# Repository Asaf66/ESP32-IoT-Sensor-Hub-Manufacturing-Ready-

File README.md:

# ESP32-C3 Multi-Sensor IoT & Data Logger
hardware system based on ESP32-C3 (RISC-V architecture) on a 4-layer PCB for noise immunity. 

The project includes sensors (environment, light, and sound), smart power and charging management (MCP73871), and a user interface.
The system supports local data storage via SD card and external flash memory via SPI connection, with Wi-Fi and BLE connectivity.

1) All-in-One Sensing Solution: Integrated temperature, humidity, light, and sound sensors, eliminating the need for multiple external modules.
2) Industrial-Grade Reliability: The 4-layer design ensures the device operates without interference in noisy industrial environments.
3) Seamless Power Integration: Built-in USB-C charging and battery management, meaning your product is portable and user-friendly from day one.
4) Rapid Manufacturing: Delivered with a full production package (Gerbers, BOM, Pick-and-Place), optimized to minimize assembly errors and part costs.

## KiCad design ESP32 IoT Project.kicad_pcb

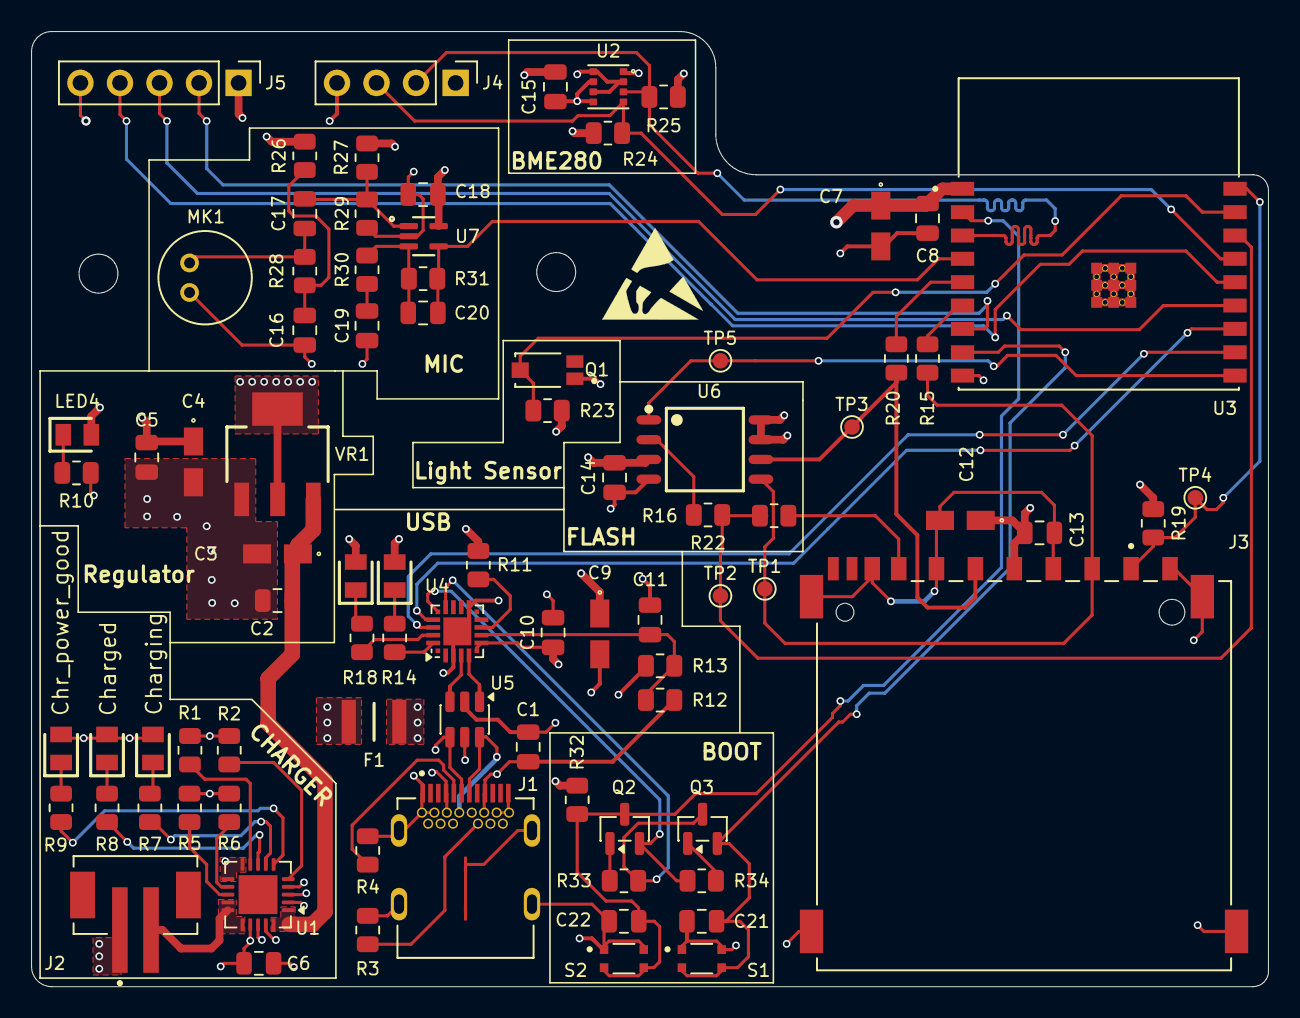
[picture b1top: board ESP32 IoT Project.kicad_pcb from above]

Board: 4 copper layers, 79.5 x 61.4 mm, 85 parts (0 on the bottom side), 58 nets.

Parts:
C1, C2, C5, C8, C10, C13, C14, C15, C18, C21: 0.1u; C_0805_2012Metric
C3, C4, C7, C12: 10u; T491A
C6, C11, C19, C22: 1u; C_0805_2012Metric
C9: 4.7u; T491A
C16: 0.1U; C_0805_2012Metric
C17: 0.01U; C_0805_2012Metric
C20: 100p; C_0805_2012Metric
F1: 0ZCH0110AF2E; FUSC3226X100N
J1: SS-52400-002; BELFUSE_SS-52400-002
J2: B2B-PH-SM4-TB; JST_B2B-PH-SM4-TB
J3: GSD090012SEU; AMPHENOL_GSD090012SEU
J4: Conn_01x04_Pin; PinHeader_1x04_P2.54mm_Vertical
J5: Conn_01x05_Pin; PinHeader_1x05_P2.54mm_Vertical
LED1, LED4, LED6: LTST-C170KRKT; LEDC2012X120N
LED2, LED5: LTST-C170GKT; LEDC2012X120N
LED3: LTST-C170TBKT; LEDC2012X120N
MK1: CMC-5042PF-AC; CUI_CMC-5042PF-AC
Q1: TEMT6000X01; TRANS_TEMT6000X01
Q2, Q3: BC817; SOT-23
R1, R2, R19, R23, R30, R32, R33, R34: 10K; R_0805_2012Metric
R3, R4: 5K1; R_0805_2012Metric
R5, R26, R28: 2K; R_0805_2012Metric
R6: 20K; R_0805_2012Metric
R7, R8, R9, R10, R14, R18: 470; R_0805_2012Metric
R11: 1K; R_0805_2012Metric
R12: 22K1; R_0805_2012Metric
R13: 47K5; R_0805_2012Metric
R15, R16, R20, R22: 50; R_0805_2012Metric
R24, R25: 4K7; R_0805_2012Metric
R27, R29: 1M; R_0805_2012Metric
R31: 100K; R_0805_2012Metric
S1: BOOT; SW_USLPT2819DT2TR
S2: RESET; SW_USLPT2819DT2TR
TP1, TP2, TP3, TP4, TP5: TestPoint; TestPoint_Pad_D1.0mm
U1: MCP73871-2CAI_ML; QFN-20-1EP_4x4mm_P0.5mm_EP2.5x2.5mm
U2: BME280; PSON65P250X250X100-8N
U3: ESP32-C3-WROOM-02-H4; MODULE_ESP32-C3-WROOM-02-H4
U4: CP2102N-Axx-xQFN20; SiliconLabs_QFN-20-1EP_3x3mm_P0.5mm_EP1.8x1.8mm
U5: USBLC6-2SC6; SOT-23-6
U6: W25Q32JVSSIQ; SOIC127P790X216-8N
U7: MAX4466EXK; SOT65P210X110-5N
VR1: LM1117MPX-3.3; VREG_LM1117MPX-3.3

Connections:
+3.3V: C4.1, C5.1, C7.1, C8.2, C9.1, C10.2, C12.1, C13.2, C14.2, C15.2, C18.1, J3.4 (VDD1), J4.1, J5.1, LED4.2 (A), LED5.2 (A), LED6.2 (A), R11.2, R19.1, R23.2, R24.2, R25.2, R26.2, R27.2, R32.1, U2.2 (CSB), U2.6 (VDDIO), U2.8 (VDD), U3.1 (3V3), U4.6 (VDD), U4.7 (VREGIN), U6.3 (~WP(IO2)), U6.7 (~HOLD/~RESET(IO3)), U6.8 (VCC), U7.5 (VCC), VR1.2 (VOUT_2), VR1.4 (VOUT_4)
+5V: C2.1, C3.1, U1.1 (OUT), U1.20 (OUT), VR1.3 (VIN)
/+5V_USB: C6.1, F1.2, LED1.2 (A), LED2.2 (A), LED3.2 (A), U1.2 (VPCC), U1.4 (PROG2), U1.17 (CE), U1.18 (IN), U1.19 (IN)
/Charged: R8.2, U1.8 (STAT1/~LBO)
/Charging: R9.2, U1.6 (~PG)
/Charging_power_good: R7.2, U1.7 (STAT2)
/ESP32-C3-02/BOOT: C21.1, Q3.2 (E), S1.3, S1.4, U3.8 (IO9)
/ESP32-C3-02/CS: TP5.1, U3.10 (IO10), U6.1 (~CS)
/ESP32-C3-02/CS_SD: J3.1 (CD/DAT3), R19.2, TP4.1, U3.18 (IO0)
/ESP32-C3-02/DTR: Q3.3 (C), R33.2, U4.15 (~CTS)
/ESP32-C3-02/EN: C22.1, Q2.3 (C), R32.2, S2.3, S2.4, U3.2 (EN)
/ESP32-C3-02/GPIO8: J5.2, U3.7 (IO8)
/ESP32-C3-02/GPIO18: J5.3, U3.13 (IO18)
/ESP32-C3-02/GPIO19: J5.4, U3.14 (IO19)
/ESP32-C3-02/MIC_OUT: C20.1, R31.1, U3.4 (IO5), U7.4 (OUT)
/ESP32-C3-02/MISO_DO: R16.1, R22.2, TP2.1, U3.16 (IO2)
/ESP32-C3-02/MOSI_DI: J3.2 (CMD), R15.1, TP1.1, U6.5 (DI(IO0))
/ESP32-C3-02/PHOTO_C: Q1.3, R23.1, U3.17 (IO1)
/ESP32-C3-02/RTS: Q2.2 (E), R34.2, U4.16 (~RTS)
/ESP32-C3-02/RX: U3.12 (TXD), U4.17 (RXD)
/ESP32-C3-02/SCL: J4.3, R24.1, U2.4 (SCK), U3.15 (IO3)
/ESP32-C3-02/SCLK: J3.5 (CLK), R20.2, TP3.1, U6.6 (CLK)
/ESP32-C3-02/SDA: J4.2, R25.1, U2.3 (SDI), U3.3 (IO4)
/ESP32-C3-02/TX: U3.11 (RXD), U4.18 (TXD)
/ESP32-C3-02/USB_D+: U4.4 (D+), U5.3 (I/O2)
/ESP32-C3-02/USB_D-: U4.5 (D-), U5.1 (I/O1)
/PWD__LED: LED4.1 (K), R10.1
/USB_DN: J1.A7 (DN1), J1.B7 (DN2), U5.6 (I/O1)
/USB_DP: J1.A6 (DP1), J1.B6 (DP2), U5.4 (I/O2)
/VBAT: J2.2, U1.14 (VBAT), U1.15 (VBAT), U1.16 (VBAT_SENSE)
/VBUS: C1.1, F1.1, J1.A4 (VBUSA1), J1.A9 (VBUSA2), J1.B4 (VBUSB1), J1.B9 (VBUSB2), R12.2, U5.5 (VBUS)
GND: C1.2, C2.2, C3.2, C4.2, C5.2, C6.2, C7.2, C8.1, C9.2, C10.1, C11.2, C12.2, C13.1, C14.1, C15.1, C16.2, C18.2, C19.2, C21.2, C22.2, J1.A1 (GNDA1), J1.A12 (GNDA2), J1.B1 (GNDB1), J1.B12 (GNDB2), J1.G1 (GND/SHIELD), J1.G2 (GND/SHIELD), J1.G3 (GND/SHIELD), J1.G4 (GND/SHIELD), J1.S1 (GND/SHIELD), J1.S2 (GND/SHIELD), J1.S3 (GND/SHIELD), J1.S4 (GND/SHIELD), J2.1, J3.3 (VSS1), J3.6 (VSS2), J3.8 (DAT1), J3.9 (DAT2), J3.G1 (SHIELD_GND), J3.G2 (SHIELD_GND), J3.G3 (SHIELD_GND), J3.G4 (SHIELD_GND), J4.4, J5.5, MK1.GND, Q1.1, R1.2, R2.2, R3.1, R4.1, R5.1, R6.1, R10.2, R13.1, R29.1, S1.1, S1.2, S2.1, S2.2, U1.3 (SEL), U1.10 (VSS), U1.11 (VSS), U2.1 (GND), U2.5 (SDO), U2.7 (GND), U3.9 (GND), U3.19 (GND), U3.20 (GND), U3.21 (GND), U3.22 (GND), U3.23 (GND), U3.24 (GND), U3.25 (GND), U3.26 (GND), U3.27 (GND), U3.28 (GND), U3.29 (GND), U3.30 (GND), U3.31 (GND), U3.32 (GND), U3.33 (GND), U3.34 (GND), U3.35 (GND), U3.36 (GND), U3.37 (GND), U3.38 (GND), U3.39 (GND), U4.3 (GND), U4.12 (GND), U4.21 (GND), U5.2 (GND), U6.4 (GND), U7.2 (GND), VR1.1 (GND)
unnamed: C16.1, R26.1, R28.2
unnamed: C17.1, MK1.OUT, R28.1
unnamed: C19.1, R30.1
unnamed: J1.A5 (CC1), R4.2
unnamed: J1.B5 (CC2), R3.2
unnamed: J3.7 (DAT0), R16.2
unnamed: LED1.1 (K), R9.1
unnamed: LED2.1 (K), R8.1
unnamed: LED3.1 (K), R7.1
unnamed: LED5.1 (K), R14.1
unnamed: LED6.1 (K), R18.1
unnamed: Q2.1 (B), R33.1
unnamed: Q3.1 (B), R34.1
unnamed: R5.2, U1.13 (PROG1)
unnamed: R6.2, U1.12 (PROG3)
unnamed: R2.1, U1.5 (THERM)
unnamed: R1.1, U1.9 (~TE)
unnamed: R20.1, U3.5 (IO6)
unnamed: R15.2, U3.6 (IO7)
unnamed: C11.1, R12.1, R13.2, U4.8 (VBUS)
unnamed: R11.1, U4.9 (~RST)
unnamed: R18.2, U4.19 (~RXT/GPIO.3)
unnamed: R14.2, U4.20 (~TXT/GPIO.2)
unnamed: R22.1, U6.2 (DO(IO1))
unnamed: C17.2, R27.1, R29.2, U7.1 (IN+)
unnamed: C20.2, R30.2, R31.2, U7.3 (IN-)

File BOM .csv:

Id,Designator,Footprint,Quantity,Designation,Supplier and ref
1,"R3,R4",R_0805_2012Metric,2,5K1,
2,"LED2,LED5",LEDC2012X120N,2,LTST-C170GKT,
3,R6,R_0805_2012Metric,1,20K,
4,"C2,C8,C18,C14,C5,C21,C1,C10,C15,C13",C_0805_2012Metric,10,0.1u,
5,R12,R_0805_2012Metric,1,22K1,
6,C16,C_0805_2012Metric,1,0.1U,
7,"LED4,LED6,LED1",LEDC2012X120N,3,LTST-C170KRKT,
8,"R5,R26,R28",R_0805_2012Metric,3,2K,
9,"C22,C11,C19,C6",C_0805_2012Metric,4,1u,
10,LED3,LEDC2012X120N,1,LTST-C170TBKT,
11,Q1,TRANS_TEMT6000X01,1,TEMT6000X01,
12,S2,SW_USLPT2819DT2TR,1,RESET,
13,U6,SOIC127P790X216-8N,1,W25Q32JVSSIQ,
14,"R7,R14,R9,R8,R18,R10",R_0805_2012Metric,6,470,
15,"R15,R22,R16,R20",R_0805_2012Metric,4,50,
16,U7,SOT65P210X110-5N,1,MAX4466EXK,
17,"R27,R29",R_0805_2012Metric,2,1M,
18,"R24,R25",R_0805_2012Metric,2,4K7,
19,U5,SOT-23-6,1,USBLC6-2SC6,
20,"TP3,TP5,TP4,TP2,TP1",TestPoint_Pad_D1.0mm,5,TestPoint,
21,J4,PinHeader_1x04_P2.54mm_Vertical,1,Conn_01x04_Pin,
22,U2,PSON65P250X250X100-8N,1,BME280,
23,"R23,R19,R33,R32,R34,R30,R2,R1",R_0805_2012Metric,8,10K,
24,J5,PinHeader_1x05_P2.54mm_Vertical,1,Conn_01x05_Pin,
25,"Q2,Q3",SOT-23,2,BC817,
26,U4,SiliconLabs_QFN-20-1EP_3x3mm_P0.5mm_EP1.8x1.8mm,1,CP2102N-Axx-xQFN20,
27,F1,FUSC3226X100N,1,0ZCH0110AF2E,
28,S1,SW_USLPT2819DT2TR,1,BOOT,
29,R11,R_0805_2012Metric,1,1K,
30,U3,MODULE_ESP32-C3-WROOM-02-H4,1,ESP32-C3-WROOM-02-H4,
31,U1,QFN-20-1EP_4x4mm_P0.5mm_EP2.5x2.5mm,1,MCP73871-2CAI_ML,
32,C9,T491A,1,4.7u,
33,J2,JST_B2B-PH-SM4-TB,1,B2B-PH-SM4-TB,
34,C17,C_0805_2012Metric,1,0.01U,
35,C20,C_0805_2012Metric,1,100p,
36,R13,R_0805_2012Metric,1,47K5,
37,"C12,C3,C7,C4",T491A,4,10u,
38,MK1,CUI_CMC-5042PF-AC,1,CMC-5042PF-AC,
39,R31,R_0805_2012Metric,1,100K,
40,J1,BELFUSE_SS-52400-002,1,SS-52400-002,
41,VR1,VREG_LM1117MPX-3.3,1,LM1117MPX-3.3,
42,J3,AMPHENOL_GSD090012SEU,1,GSD090012SEU,

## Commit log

2026-05-05 Add images to README for project visualization
    Added images to enhance project documentation.
2026-05-05 Add additional images to README.md
2026-05-05 Create 3D View
2026-05-13 Update project title and description in README
